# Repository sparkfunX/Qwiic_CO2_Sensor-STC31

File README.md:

SparkX CO<sub>2</sub> Sensor - STC31 (Qwiic)
========================================

[*SparkX CO2 Sensor - STC31 (Qwiic) (SPX-18385)*](https://www.sparkfun.com/products/18385)

Do you need to be able to sense CO<sub>2</sub> concentrations of up to 100%? If so, the STC31 is the sensor for you!
The Sensirion STC31 thermal conductivity sensor has two CO<sub>2</sub> measurement ranges: 0 to 25 vol%; and 0 to 100 vol%.
The measurement repeatability is 0.2 vol%, with a stability of 0.025 vol% / °C.
The measurement accuracy depends on the measurement range: 0.5 vol% + 3% measured value; 1 vol% + 3% measured value.

Our breakout includes a separate SHTC3 humidity and temperature sensor; allowing the STC31 to deliver humidity-compensated
measurements together with improved temperature compensation. The STC31 can compensate for atmospheric pressure too - which is handy if,
like us, you’re up in the mountains!

The STC3x sensor family is Sensirion’s series of Gas Concentration sensors designed for high-volume applications.
The STC3x utilizes a revolutionized thermal conductivity measurement principle, which results in superior repeatability and long-term stability.
This makes the STC31 a perfect choice for applications where reliability is key.

The outstanding performance of these sensors is based on Sensirion’s patented CMOSens® sensor technology, which combines the sensor element,
signal processing and digital calibration on a small CMOS chip.
The well-proven CMOS technology is perfectly suited for high-quality mass production and is the ideal choice for demanding and cost-sensitive OEM applications.

Repository Contents
-------------------
* **/Documents** - datasheets etc.
* **/Hardware** - Eagle design files (.brd, .sch)
- **LICENSE.md** contains the licence information

Documentation
--------------
* **[STC3x Arduino Library](https://github.com/sparkfun/SparkFun_STC3x_Arduino_Library)** - Arduino library for the SparkX CO2 Sensor - STC31.
* **[Hookup Guide]()** - Basic hookup guide for the SparkX CO2 Sensor - STC31.

Product Versions
----------------
* [SPX-18385](https://www.sparkfun.com/products/18385) - Original SparkX Release.

License Information
-------------------

This product is _**open source**_!

Please review the LICENSE.md file for license information.

If you have any questions or concerns on licensing, please contact technical support on our [SparkFun forums](https://forum.sparkfun.com/viewforum.php?f=123).

Distributed as-is; no warranty is given.

- Your friends at SparkFun.

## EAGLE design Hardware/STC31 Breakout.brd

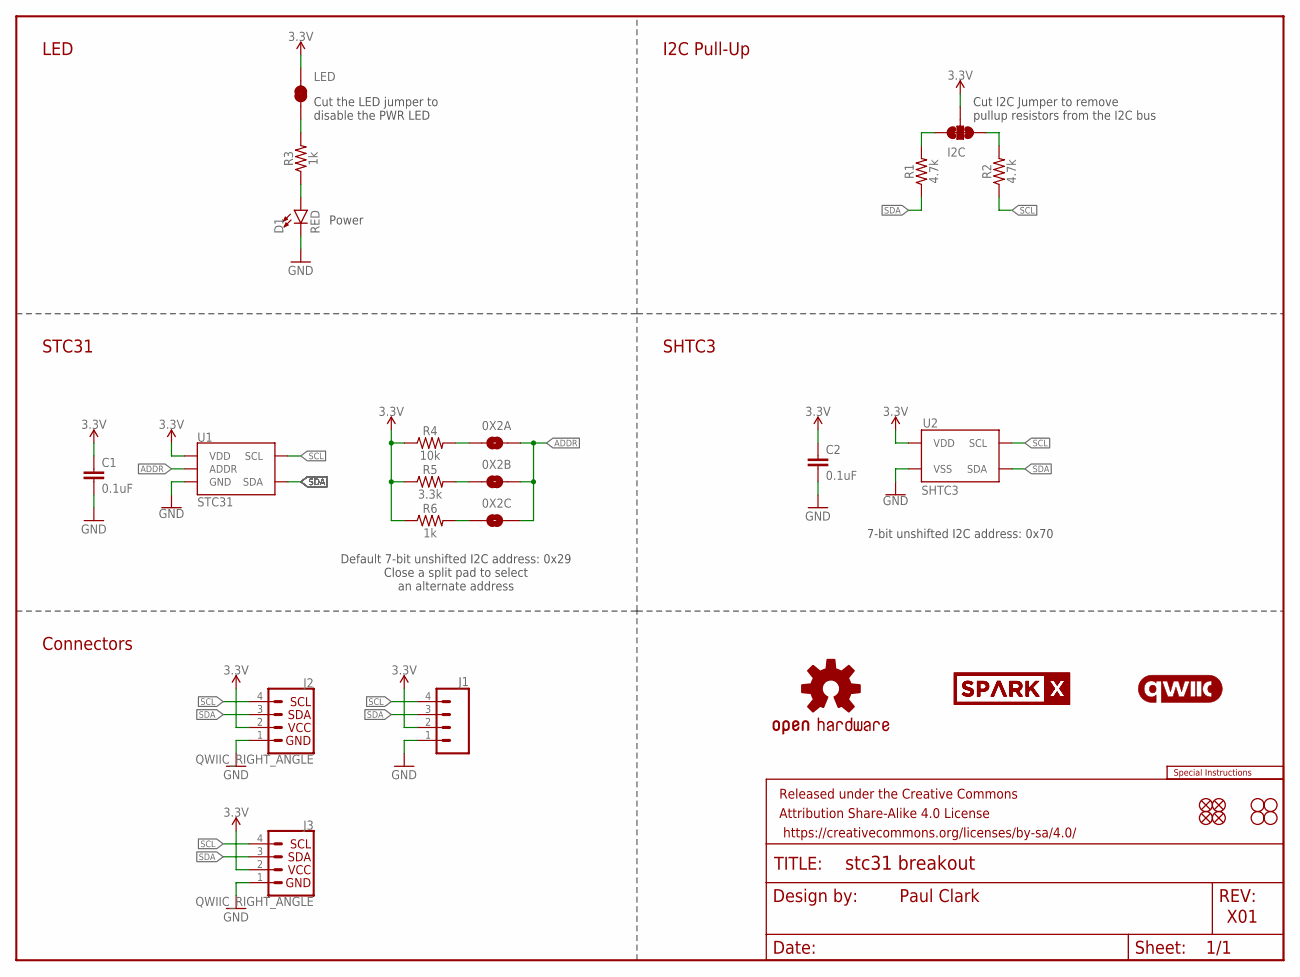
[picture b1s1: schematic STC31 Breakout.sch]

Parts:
0X2A, 0X2B, 0X2C: JUMPER-SMT_2_NO_SILK; SMT-JUMPER_2_NO_SILK
C1, C2: 0.1uF; 0603
D1: RED; LED-0603
FRAME1: FRAME-LETTER; CREATIVE_COMMONS
I2C: JUMPER-SMT_3_2-NC_TRACE_SILK; SMT-JUMPER_3_2-NC_TRACE_SILK
J1: CONN_041X04_NO_SILK; 1X04_NO_SILK
J2, J3: QWIIC_RIGHT_ANGLE; JST04_1MM_RA
JP1, JP2, JP5, JP6: FIDUCIAL1X2; FIDUCIAL-1X2
JP3, JP4, JP7, JP8: STAND-OFF
LED: JUMPER-SMT_2_NC_TRACE_SILK; SMT-JUMPER_2_NC_TRACE_SILK
LOGO1: SPECIAL_INSTRUCTIONS-ORDERING; ORDERING_INSTRUCTIONS
LOGO2: QWIIC_LOGO_5MM; QWIIC_5MM
LOGO5: OSHW-LOGOS; OSHW-LOGO-S
R1, R2: 4.7k; 0603
R3, R6: 1k; 0603
R4: 10k; 0603
R5: 3.3k; 0603
U1: STC31
U2: SHTC3
U$10, U$18: SPARKX-LOGO3; SPARKX-SMALL

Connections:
3.3V: C1.1, C2.1, I2C.2, J1.2, J2.2, J3.2, LED.2, R4.1, R5.1, R6.1, U1.6 (VDD), U2.1 (VDD)
ADDR: 0X2A.2, 0X2B.2, 0X2C.2, U1.3 (ADDR)
GND: C1.2, C2.2, D1.C, J1.1, J2.1, J3.1, U1.1 (GND), U1.5 (GND), U1.9 (GND), U1.11 (GND), U1.DIEPAD (GND), U2.4 (VSS), U2.5 (VSS)
unnamed: LED.1, R3.2
unnamed: I2C.3, R1.2
unnamed: D1.A, R3.1
unnamed: I2C.1, R2.2
unnamed: 0X2A.1, R4.2
unnamed: 0X2B.1, R5.2
unnamed: 0X2C.1, R6.2
SCL: J1.4, J2.4, J3.4, R2.1, U1.4 (SCL), U2.2 (SCL)
SDA: J1.3, J2.3, J3.3, R1.1, U1.7 (SDA), U2.3 (SDA)

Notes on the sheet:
Paul Clark
X01
7-bit unshifted I2C address: 0x70
Power
I2C Pull-Up
STC31
Connectors
Cut the LED jumper to disable the PWR LED
Cut I2C Jumper to remove pullup resistors from the I2C bus
LED
SHTC3
Default 7-bit unshifted I2C address: 0x29 Close a split pad to select an alternate address

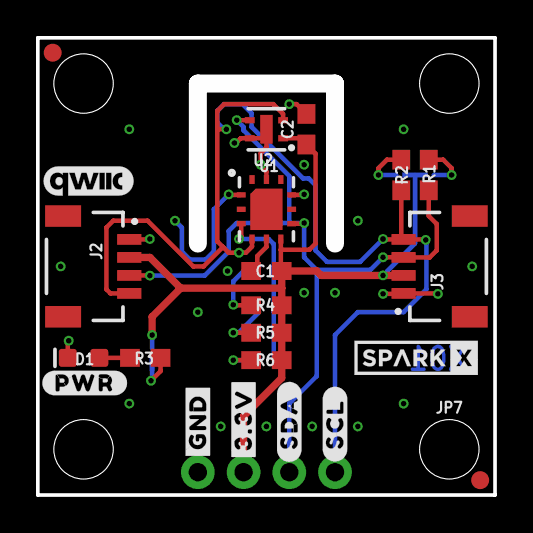
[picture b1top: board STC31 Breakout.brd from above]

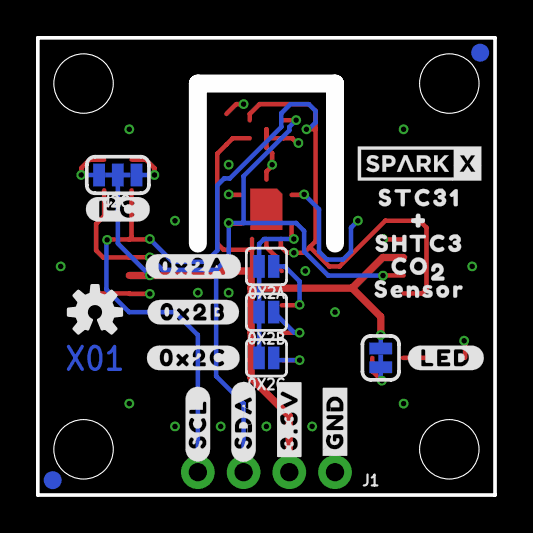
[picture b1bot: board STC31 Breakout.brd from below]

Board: 2 copper layers, 25.4 x 25.4 mm, 53 parts (25 on the bottom side), 12 nets.

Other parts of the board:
U$1, U$33: #GND#0
U$2, U$34: #3#3V#0
U$3, U$35: #SDA#0
U$4, U$36: #SCL#0
U$5: #LED#0
U$6: #0X2A#0
U$7: #0X2B#0
U$8: #0X2C#0
U$9: #I�C#0
U$11: STC310
U$12: #0
U$13: SHTC30
U$14: CO0
U$15: 20
U$16: SENSOR0
U$32: #PWR#0

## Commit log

2021-06-17 Add PROD_ID for STC31
2021-08-06 Add product image

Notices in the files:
parts and their libraries:
SparkFun-Resistors: Licensing: Creative Commons ShareAlike 4.0 International - https://creativecommons.org/licenses/by-sa/4.0
SparkFun-Aesthetics: Released under the Creative Commons Attribution Share-Alike 4.0 License
SparkFun-Aesthetics: https://creativecommons.org/licenses/by-sa/4.0
